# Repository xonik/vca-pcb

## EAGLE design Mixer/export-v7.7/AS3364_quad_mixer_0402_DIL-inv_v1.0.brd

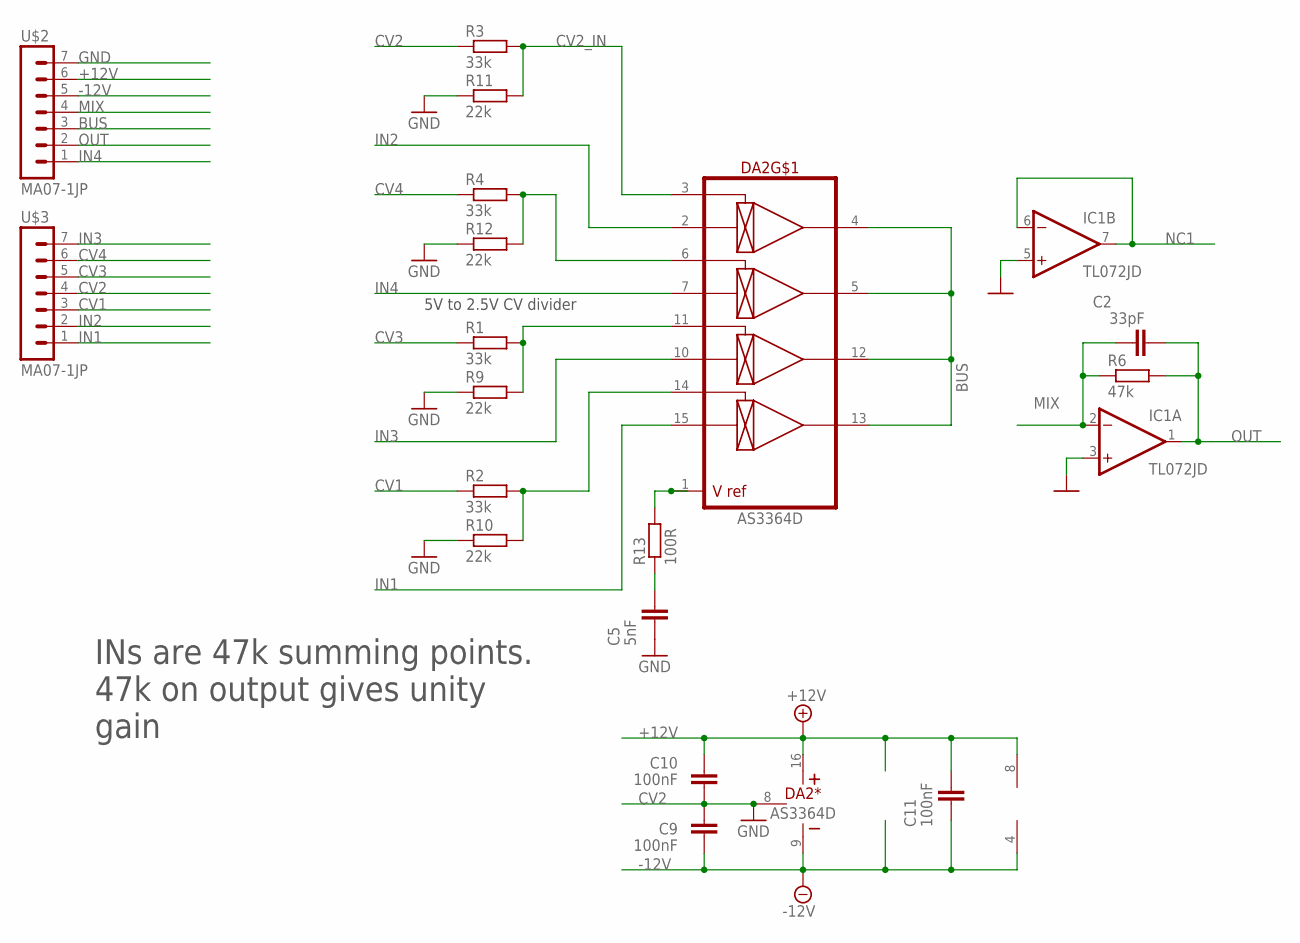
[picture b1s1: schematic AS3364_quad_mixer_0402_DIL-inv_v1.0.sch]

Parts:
C2: 33pF; C0402
C5: 5nF; C0402
C9, C10, C11: 100nF; C0402
DA2: AS3364D; DIL16J
IC1: TL072JD; SO08J
R1, R2, R3, R4: 33k; R0402
R6: 47k; R0402
R9, R10, R11, R12: 22k; R0402
R13: 100R; R0402
U$2, U$3: MA07-1JP; SIP-PIN07-1J

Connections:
+12V: C10.2, C11.2, DA2.16 (V+), IC1.8 (V+), U$2.6
-12V: C9.1, C11.1, DA2.9 (V-), IC1.4 (V-), U$2.5
BUS: DA2.4 (OUT1), DA2.5 (OUT2), DA2.12 (OUT3), DA2.13 (OUT4), U$2.3
CV1: R2.1, U$3.3
CV2: R3.1, U$3.4
CV2_IN: DA2.3 (CV1), R3.2, R11.2
CV3: R1.1, U$3.5
CV4: R4.1, U$3.6
GND: C5.1, C9.2, C10.1, DA2.8 (GND), IC1.3 (+IN), IC1.5 (+IN), R9.1, R10.1, R11.1, R12.1, U$2.7
IN1: DA2.15 (IN4), U$3.1
IN2: DA2.2 (IN1), U$3.2
IN3: DA2.10 (IN3), U$3.7
IN4: DA2.7 (IN2), U$2.1
MIX: C2.1, IC1.2 (-IN), R6.1, U$2.4
unnamed: DA2.1 (VREF), R13.2
unnamed: DA2.6 (CV2), R4.2, R12.2
unnamed: DA2.11 (CV3), R1.2, R9.2
unnamed: C5.2, R13.1
unnamed: DA2.14 (CV4), R2.2, R10.2
NC1: IC1.6 (-IN), IC1.7 (OUT)
OUT: C2.2, IC1.1 (OUT), R6.2, U$2.2

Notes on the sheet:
INs are 47k summing points. 47k on output gives unity gain
5V to 2.5V CV divider

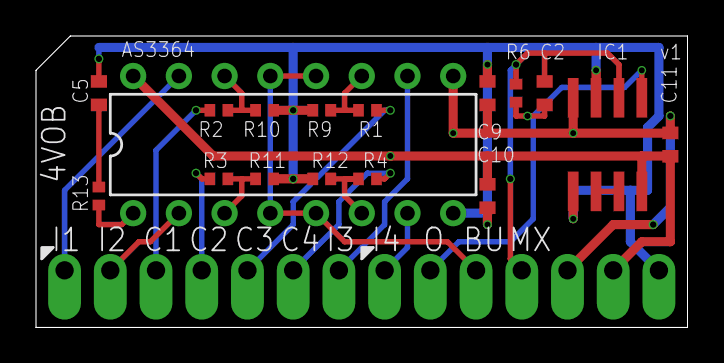
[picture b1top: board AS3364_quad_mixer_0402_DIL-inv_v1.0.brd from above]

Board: 2 copper layers, 36.2 x 16.2 mm, 20 parts (1 on the bottom side), 21 nets.

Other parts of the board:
U$1: XONIK_LOGO_18

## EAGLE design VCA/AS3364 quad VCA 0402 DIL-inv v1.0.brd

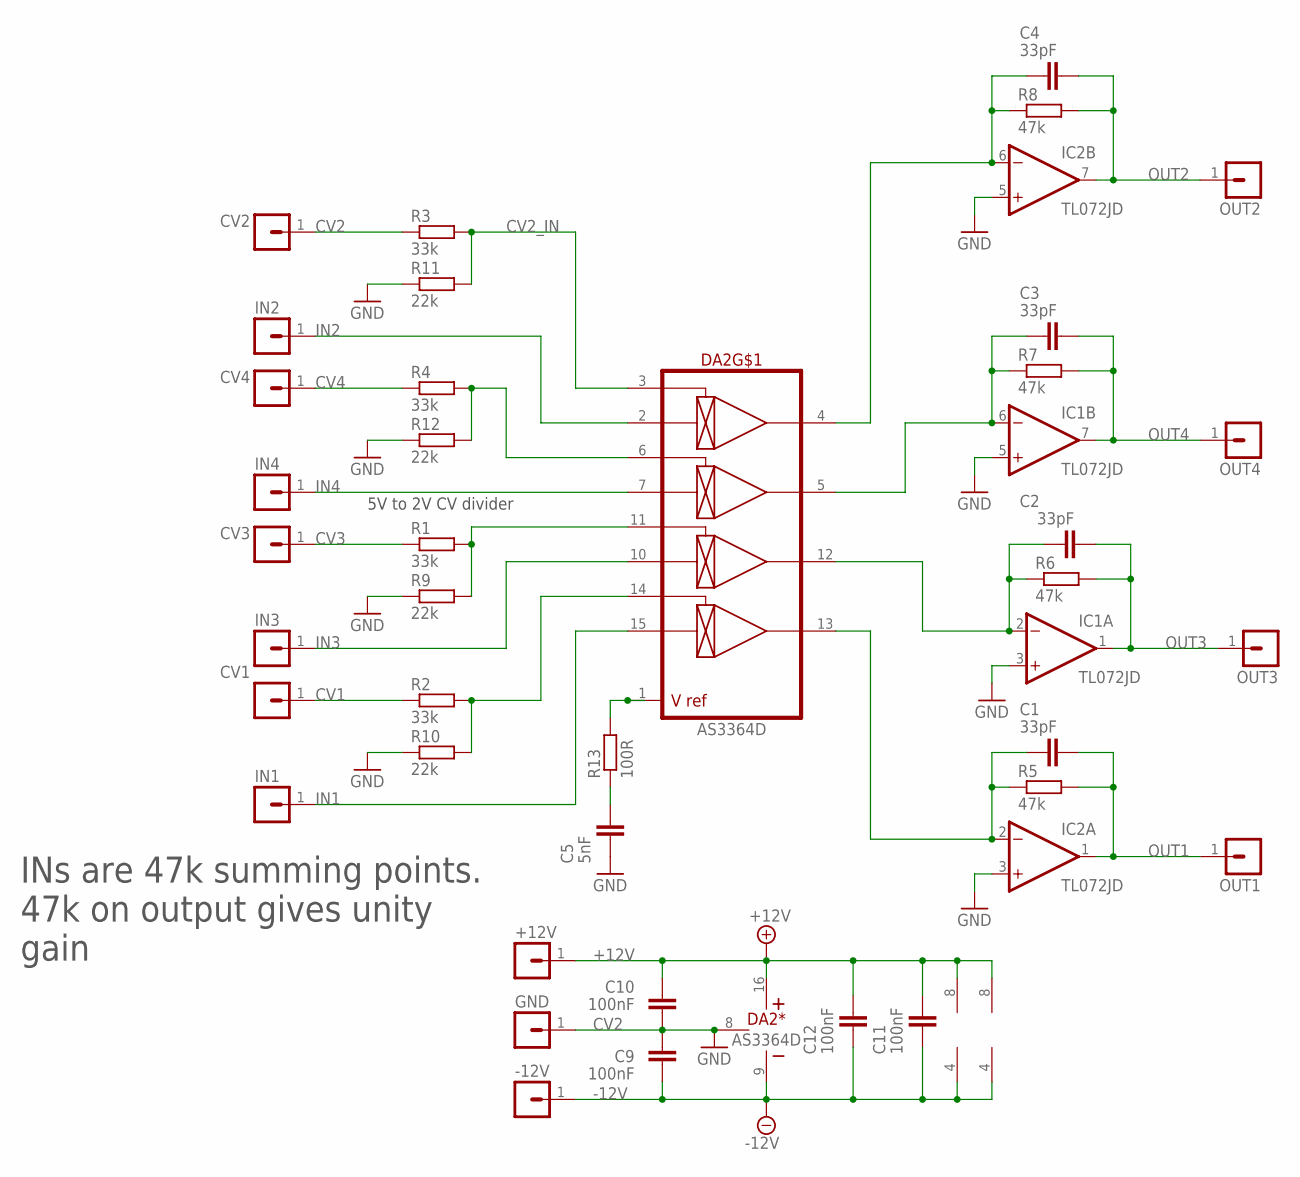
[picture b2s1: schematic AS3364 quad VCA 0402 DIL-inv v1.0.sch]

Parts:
+12V: MA01-1JP; SIP-PIN01-1J
-12V: MA01-1JP; SIP-PIN01-1J
C1, C2, C3, C4: 33pF; C0402
C5: 5nF; C0402
C9, C10, C11, C12: 100nF; C0402
CV1, CV2, CV3, CV4: MA01-1JP; SIP-PIN01-1J
DA2: AS3364D; DIL16J
GND: MA01-1JP; SIP-PIN01-1J
IC1, IC2: TL072JD; SO08J
IN1, IN2, IN3, IN4: MA01-1JP; SIP-PIN01-1J
OUT1, OUT2, OUT3, OUT4: MA01-1JP; SIP-PIN01-1J
R1, R2, R3, R4: 33k; R0402
R5, R6, R7, R8: 47k; R0402
R9, R10, R11, R12: 22k; R0402
R13: 100R; R0402

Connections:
+12V: +12V.1, C10.2, C11.2, C12.2, DA2.16 (V+), IC1.8 (V+), IC2.8 (V+)
-12V: -12V.1, C9.1, C11.1, C12.1, DA2.9 (V-), IC1.4 (V-), IC2.4 (V-)
CV1: CV1.1, R2.1
CV2: CV2.1, R3.1
CV2_IN: DA2.3 (CV1), R3.2, R11.2
CV3: CV3.1, R1.1
CV4: CV4.1, R4.1
GND: C5.1, C9.2, C10.1, DA2.8 (GND), GND.1, IC1.3 (+IN), IC1.5 (+IN), IC2.3 (+IN), IC2.5 (+IN), R9.1, R10.1, R11.1, R12.1
IN1: DA2.15 (IN4), IN1.1
IN2: DA2.2 (IN1), IN2.1
IN3: DA2.10 (IN3), IN3.1
IN4: DA2.7 (IN2), IN4.1
unnamed: C4.1, DA2.4 (OUT1), IC2.6 (-IN), R8.1
unnamed: DA2.1 (VREF), R13.2
unnamed: C3.1, DA2.5 (OUT2), IC1.6 (-IN), R7.1
unnamed: C2.1, DA2.12 (OUT3), IC1.2 (-IN), R6.1
unnamed: C1.1, DA2.13 (OUT4), IC2.2 (-IN), R5.1
unnamed: DA2.6 (CV2), R4.2, R12.2
unnamed: DA2.11 (CV3), R1.2, R9.2
unnamed: C5.2, R13.1
unnamed: DA2.14 (CV4), R2.2, R10.2
OUT1: C1.2, IC2.1 (OUT), OUT1.1, R5.2
OUT2: C4.2, IC2.7 (OUT), OUT2.1, R8.2
OUT3: C2.2, IC1.1 (OUT), OUT3.1, R6.2
OUT4: C3.2, IC1.7 (OUT), OUT4.1, R7.2

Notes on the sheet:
INs are 47k summing points. 47k on output gives unity gain
5V to 2V CV divider

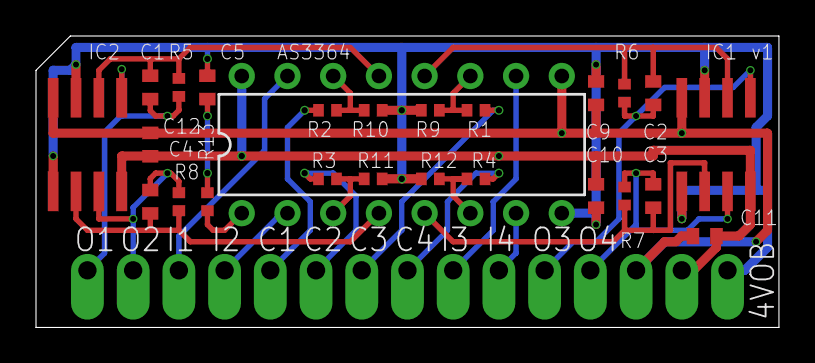
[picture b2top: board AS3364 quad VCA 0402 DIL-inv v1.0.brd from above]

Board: 2 copper layers, 41.3 x 16.2 mm, 41 parts (1 on the bottom side), 25 nets.

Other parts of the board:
U$1: XONIK_LOGO_18

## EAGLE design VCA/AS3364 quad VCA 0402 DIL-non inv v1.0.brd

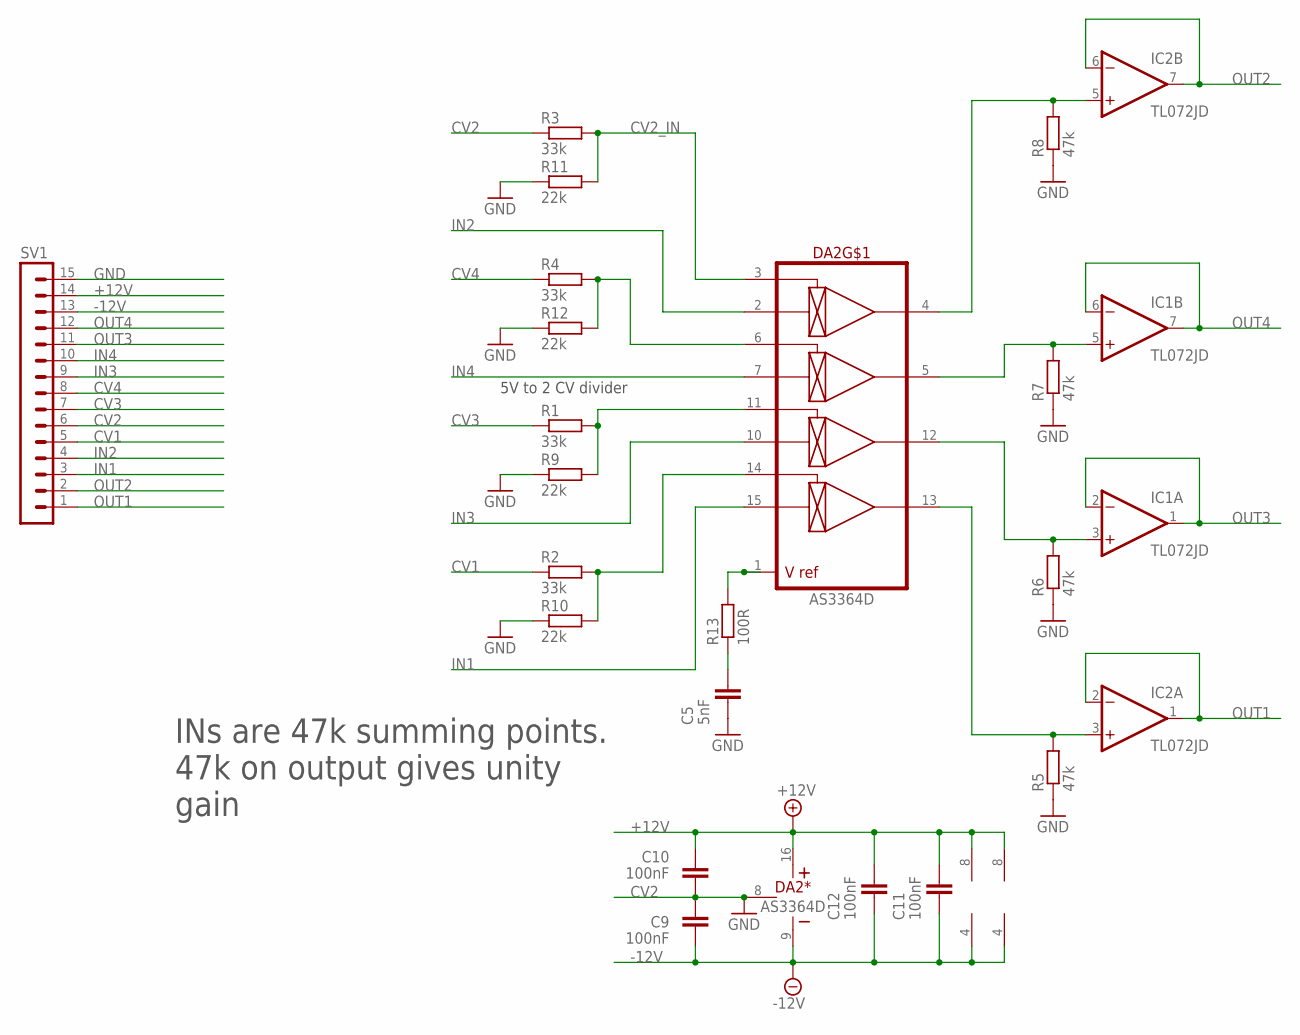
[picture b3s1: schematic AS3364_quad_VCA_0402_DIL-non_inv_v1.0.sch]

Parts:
C5: 5nF; C0402
C9, C10, C11, C12: 100nF; C0402
DA2: AS3364D; DIL16J
IC1, IC2: TL072JD; SO08J
R1, R2, R3, R4: 33k; R0402
R5, R6, R7, R8: 47k; R0402
R9, R10, R11, R12: 22k; R0402
R13: 100R; R0402
SV1: MA15-1JP; SIP-PIN15-1J

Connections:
+12V: C10.2, C11.2, C12.2, DA2.16 (V+), IC1.8 (V+), IC2.8 (V+), SV1.14
-12V: C9.1, C11.1, C12.1, DA2.9 (V-), IC1.4 (V-), IC2.4 (V-), SV1.13
CV1: R2.1, SV1.5
CV2: R3.1, SV1.6
CV2_IN: DA2.3 (CV1), R3.2, R11.2
CV3: R1.1, SV1.7
CV4: R4.1, SV1.8
GND: C5.1, C9.2, C10.1, DA2.8 (GND), R5.1, R6.1, R7.1, R8.1, R9.1, R10.1, R11.1, R12.1, SV1.15
IN1: DA2.15 (IN4), SV1.3
IN2: DA2.2 (IN1), SV1.4
IN3: DA2.10 (IN3), SV1.9
IN4: DA2.7 (IN2), SV1.10
unnamed: DA2.1 (VREF), R13.2
unnamed: DA2.4 (OUT1), IC2.5 (+IN), R8.2
unnamed: DA2.5 (OUT2), IC1.5 (+IN), R7.2
unnamed: DA2.6 (CV2), R4.2, R12.2
unnamed: DA2.12 (OUT3), IC1.3 (+IN), R6.2
unnamed: DA2.11 (CV3), R1.2, R9.2
unnamed: DA2.13 (OUT4), IC2.3 (+IN), R5.2
unnamed: C5.2, R13.1
unnamed: DA2.14 (CV4), R2.2, R10.2
OUT1: IC2.1 (OUT), IC2.2 (-IN), SV1.1
OUT2: IC2.6 (-IN), IC2.7 (OUT), SV1.2
OUT3: IC1.1 (OUT), IC1.2 (-IN), SV1.11
OUT4: IC1.6 (-IN), IC1.7 (OUT), SV1.12

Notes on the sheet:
INs are 47k summing points. 47k on output gives unity gain
5V to 2 CV divider

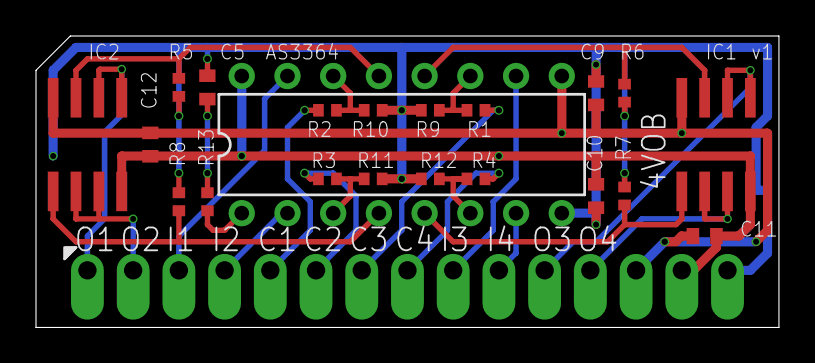
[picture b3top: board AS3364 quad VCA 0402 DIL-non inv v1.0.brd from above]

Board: 2 copper layers, 41.3 x 16.2 mm, 23 parts (1 on the bottom side), 25 nets.

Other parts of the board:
U$1: XONIK_LOGO_18

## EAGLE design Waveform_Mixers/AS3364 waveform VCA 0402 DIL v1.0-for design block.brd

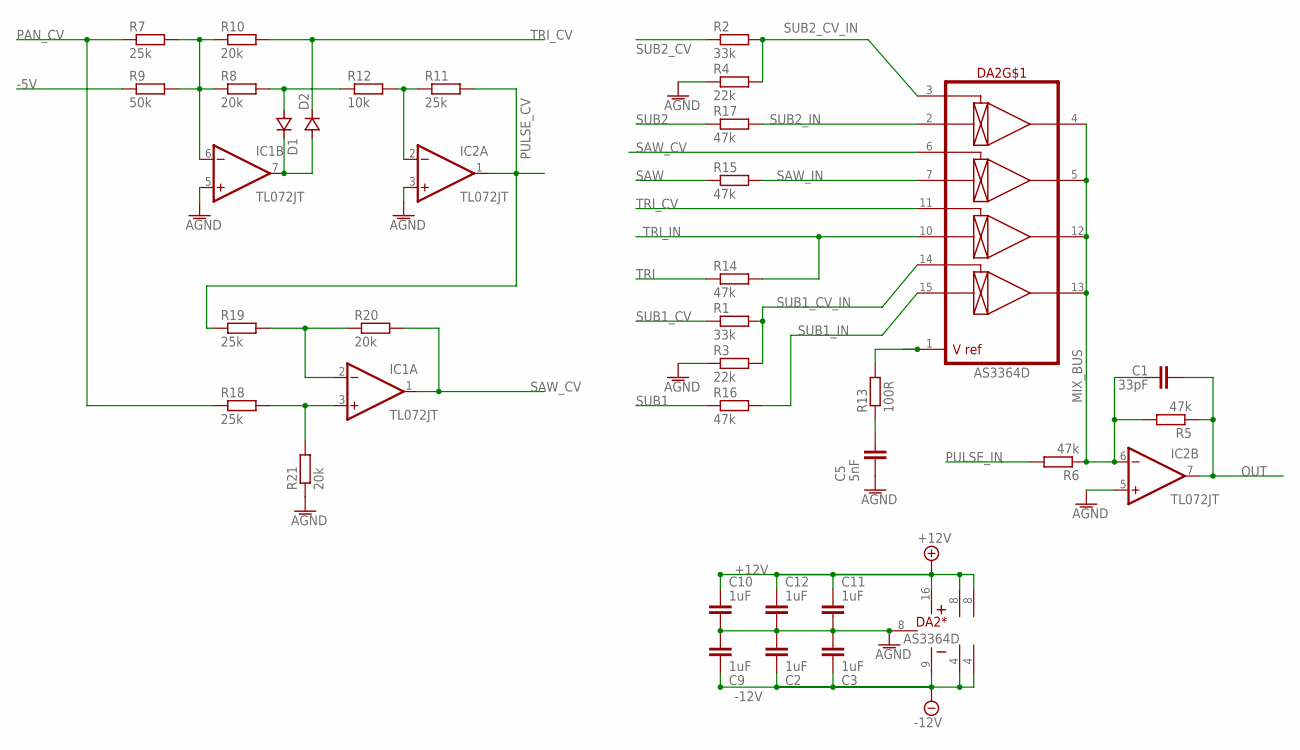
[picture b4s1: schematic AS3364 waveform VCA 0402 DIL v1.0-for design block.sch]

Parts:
C1: 33pF; C0402-J
C2, C3, C9, C10, C11, C12: 1uF; C0402-J
C5: 5nF; C0402-J
D1, D2: DIODESOD323; SOD323J
DA2: AS3364D; DIL16J
IC1, IC2: TL072JT; TSSOP8J
R1, R2: 33k; R0402
R3, R4: 22k; R0402
R5, R6, R14, R15, R16, R17: 47k; R0402
R7, R11, R18, R19: 25k; R0402
R8, R10, R20, R21: 20k; R0402
R9: 50k; R0402
R12: 10k; R0402
R13: 100R; R0402

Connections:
+12V: C10.2, C11.2, C12.2, DA2.16 (V+), IC1.8 (V+), IC2.8 (V+)
-5V: R9.1
-12V: C2.1, C3.1, C9.1, DA2.9 (V-), IC1.4 (V-), IC2.4 (V-)
AGND: C2.2, C3.2, C5.1, C9.2, C10.1, C11.1, C12.1, DA2.8 (GND), IC1.5 (+IN), IC2.3 (+IN), IC2.5 (+IN), R3.1, R4.1, R21.1
MIX_BUS: C1.2, DA2.4 (OUT1), DA2.5 (OUT2), DA2.12 (OUT3), DA2.13 (OUT4), IC2.6 (-IN), R5.2, R6.1
unnamed: DA2.1 (VREF), R13.2
unnamed: D1.1 (C), D2.2 (A), IC1.7 (OUT)
unnamed: IC1.6 (-IN), R7.2, R8.1, R9.2, R10.1
unnamed: IC1.3 (+IN), R18.2, R21.2
unnamed: C5.2, R13.1
unnamed: IC1.2 (-IN), R19.2, R20.1
unnamed: IC2.2 (-IN), R11.1, R12.2
unnamed: D1.2 (A), R8.2, R12.1
OUT: C1.1, IC2.7 (OUT), R5.1
PAN_CV: R7.1, R18.1
PULSE_CV: IC2.1 (OUT), R11.2, R19.1
PULSE_IN: R6.2
SAW: R15.1
SAW_CV: DA2.6 (CV2), IC1.1 (OUT), R20.2
SAW_IN: DA2.7 (IN2), R15.2
SUB1: R16.1
SUB1_CV: R1.1
SUB1_CV_IN: DA2.14 (CV4), R1.2, R3.2
SUB1_IN: DA2.15 (IN4), R16.2
SUB2: R17.1
SUB2_CV: R2.1
SUB2_CV_IN: DA2.3 (CV1), R2.2, R4.2
SUB2_IN: DA2.2 (IN1), R17.2
TRI: R14.1
TRI_CV: D2.1 (C), DA2.11 (CV3), R10.2
TRI_IN: DA2.10 (IN3), R14.2

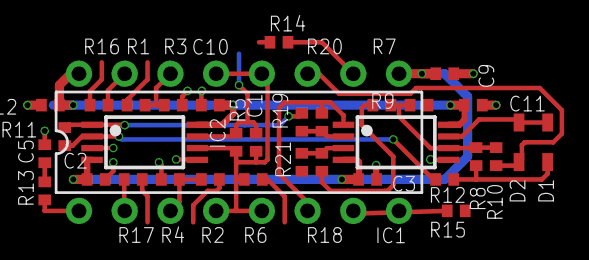
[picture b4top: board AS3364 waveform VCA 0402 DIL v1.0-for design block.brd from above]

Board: 2 copper layers, 34 parts (0 on the bottom side), 23 nets.
